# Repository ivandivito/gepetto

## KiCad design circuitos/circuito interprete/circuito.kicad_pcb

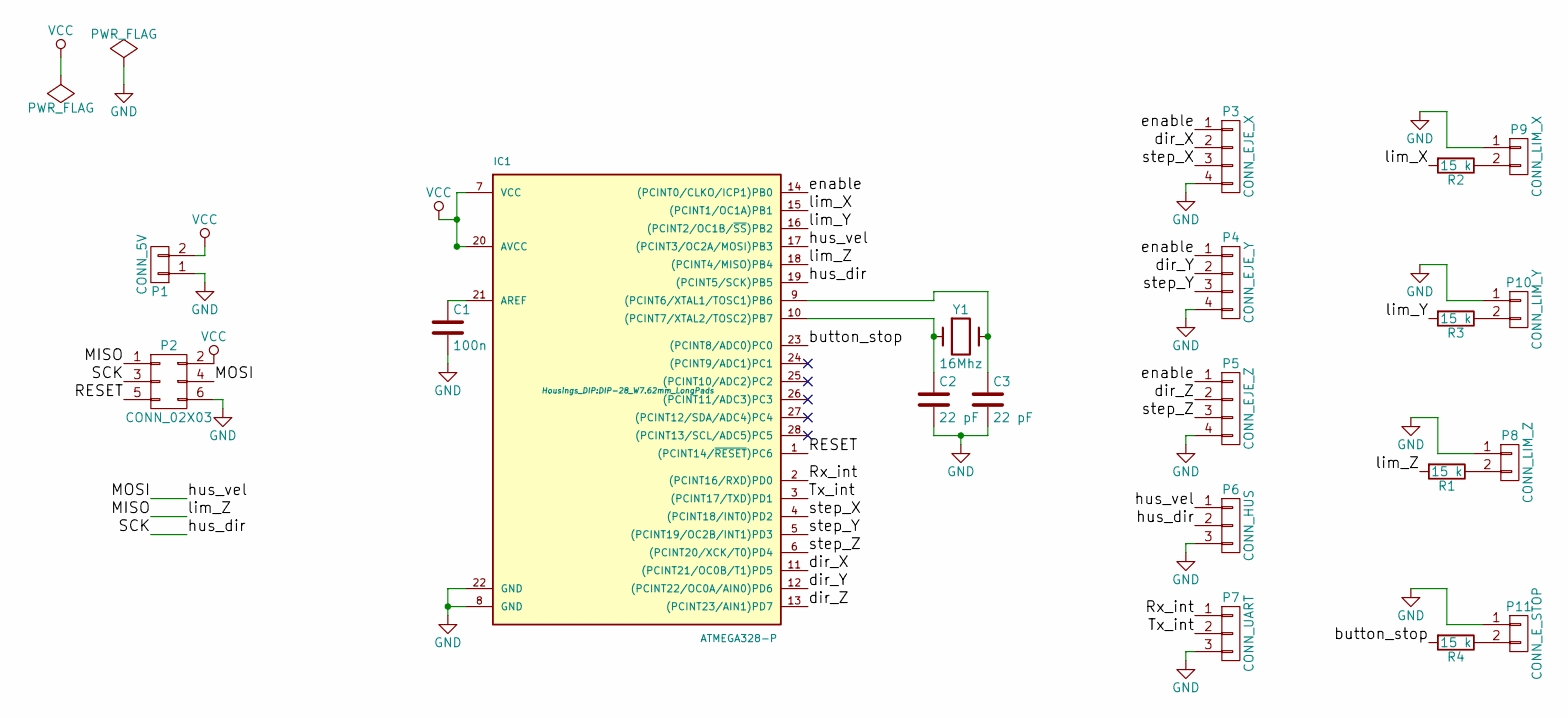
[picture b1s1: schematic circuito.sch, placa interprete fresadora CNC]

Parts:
C1: 100n; C_Disc_D3_P2.5
C2, C3: 22 pF; C_Disc_D3_P2.5
IC1: ATMEGA328-P; DIP-28_W7.62mm_LongPads
P1: CONN_5V; Pin_Header_Straight_1x02
P2: CONN_02X03; Pin_Header_Straight_2x03
P3: CONN_EJE_X; Pin_Header_Straight_1x04
P4: CONN_EJE_Y; Pin_Header_Straight_1x04
P5: CONN_EJE_Z; Pin_Header_Straight_1x04
P6: CONN_HUS; Pin_Header_Straight_1x03
P7: CONN_UART; Pin_Header_Straight_1x03
P8: CONN_LIM_Z; Pin_Header_Straight_1x02
P9: CONN_LIM_X; Pin_Header_Straight_1x02
P10: CONN_LIM_Y; Pin_Header_Straight_1x02
P11: CONN_E_STOP; Pin_Header_Straight_1x02
R1, R2, R3, R4: 15 k; Resistor_Horizontal_RM10mm
Y1: 16Mhz; Crystal_HC48-U_Vertical

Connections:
/MISO: IC1.18 ((PCINT4/MISO)PB4), P2.1, R1.2
/MOSI: IC1.17 ((PCINT3/OC2A/MOSI)PB3), P2.4, P6.1
/RESET: IC1.1 ((PCINT14/~RESET~)PC6), P2.5
/Rx_int: IC1.2 ((PCINT16/RXD)PD0), P7.1
/SCK: IC1.19 ((PCINT5/SCK)PB5), P2.3, P6.2
/Tx_int: IC1.3 ((PCINT17/TXD)PD1), P7.2
/button_stop: IC1.23 ((PCINT8/ADC0)PC0), R4.2
/dir_X: IC1.11 ((PCINT21/OC0B/T1)PD5), P3.2
/dir_Y: IC1.12 ((PCINT22/OC0A/AIN0)PD6), P4.2
/dir_Z: IC1.13 ((PCINT23/AIN1)PD7), P5.2
/enable: IC1.14 ((PCINT0/CLKO/ICP1)PB0), P3.1, P4.1, P5.1
/lim_X: IC1.15 ((PCINT1/OC1A)PB1), R2.2
/lim_Y: IC1.16 ((PCINT2/OC1B/~SS~)PB2), R3.2
/step_X: IC1.4 ((PCINT18/INT0)PD2), P3.3
/step_Y: IC1.5 ((PCINT19/OC2B/INT1)PD3), P4.3
/step_Z: IC1.6 ((PCINT20/XCK/T0)PD4), P5.3
GND: C1.2, C2.2, C3.2, IC1.8 (GND), IC1.22 (GND), P1.1, P2.6, P3.4, P4.4, P5.4, P6.3, P7.3, P8.1, P9.1, P10.1, P11.1
unnamed: C1.1, IC1.21 (AREF)
unnamed: C2.1, IC1.10 ((PCINT7/XTAL2/TOSC2)PB7), Y1.1
unnamed: C3.1, IC1.9 ((PCINT6/XTAL1/TOSC1)PB6), Y1.2
unnamed: P8.2, R1.1
unnamed: P9.2, R2.1
unnamed: P10.2, R3.1
unnamed: P11.2, R4.1
VCC: IC1.7 (VCC), IC1.20 (AVCC), P1.2, P2.2

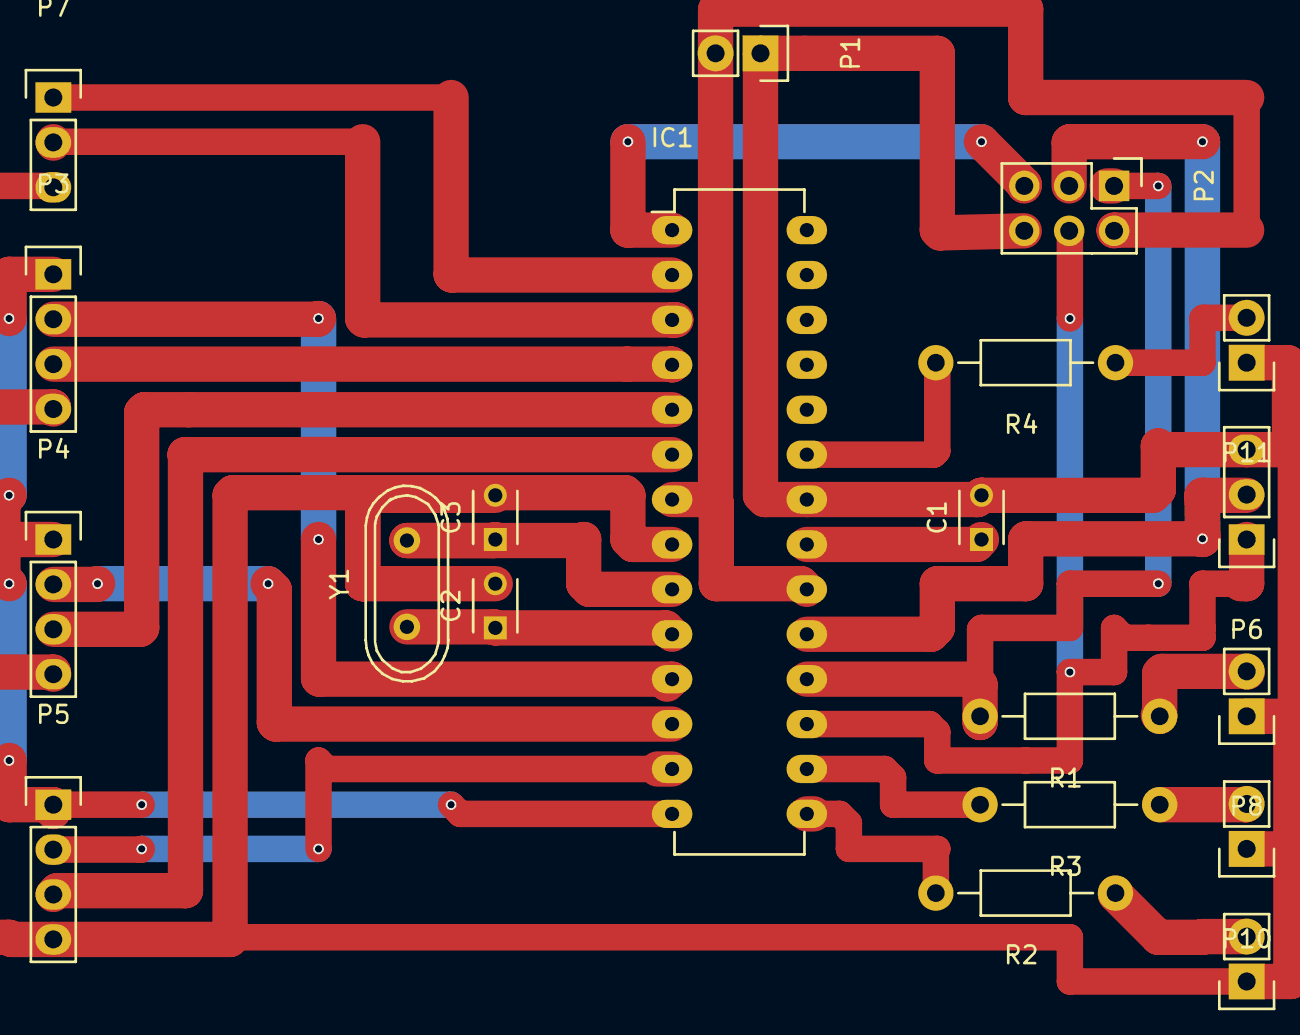
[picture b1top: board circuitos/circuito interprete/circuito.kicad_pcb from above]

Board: 2 copper layers, 20 parts (0 on the bottom side), 25 nets.

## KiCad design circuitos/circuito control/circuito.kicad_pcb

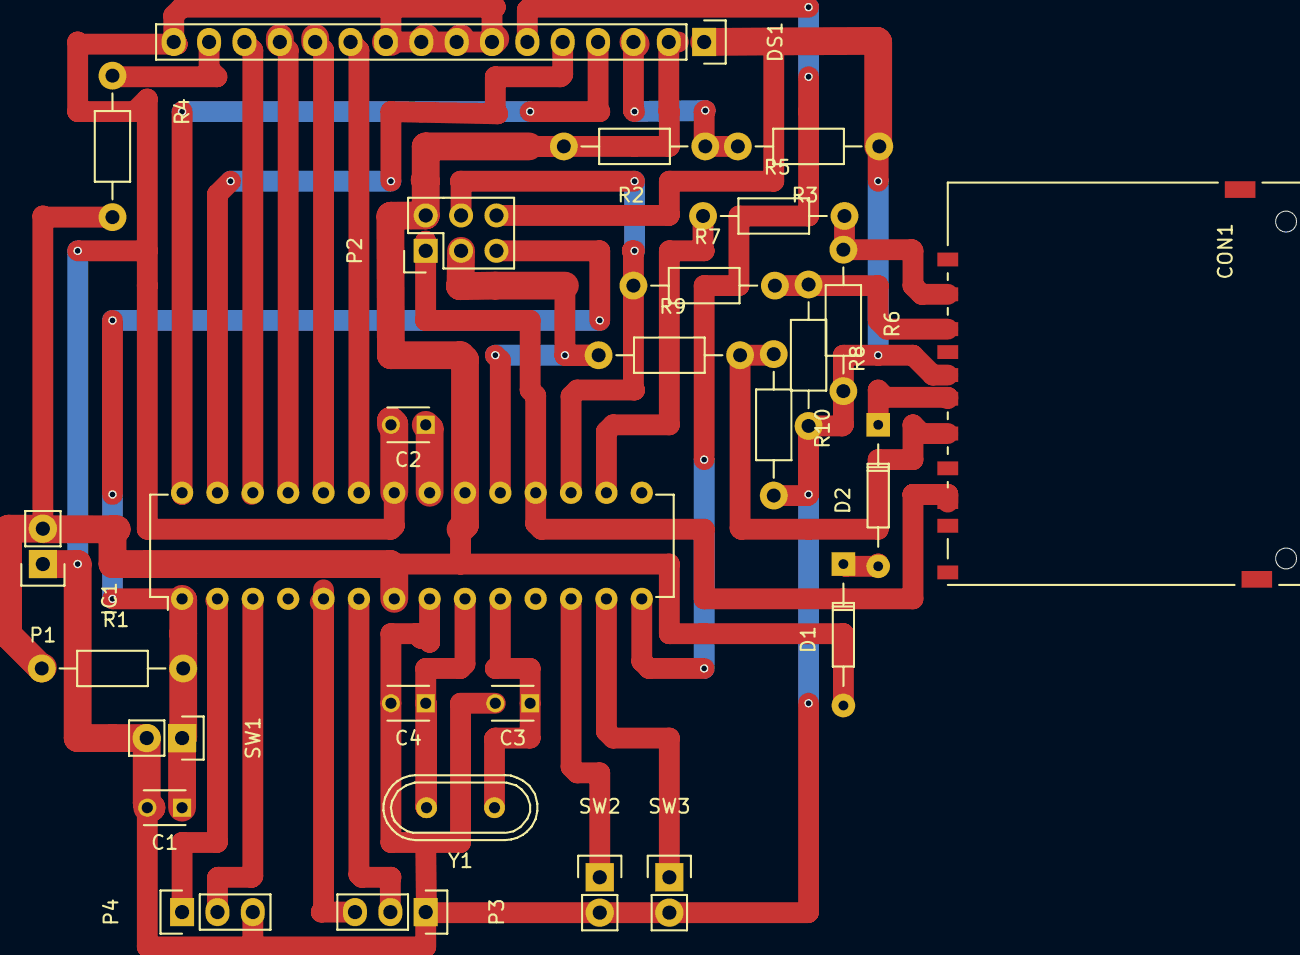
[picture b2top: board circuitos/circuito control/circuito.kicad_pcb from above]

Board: 2 copper layers, 27 parts (0 on the bottom side), 30 nets.

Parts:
C1: 100 n; C_Disc_D3_P2.5
C2: 100n; C_Disc_D3_P2.5
C3, C4: 22 pF; C_Disc_D3_P2.5
CON1: SD_Card; SD_Card_Receptacle
D1, D2: D; Diode_DO-35_SOD27_Horizontal_RM10
DS1: LCD16X2; Pin_Header_Straight_1x16
IC1: ATMEGA328-P; DIP-28_W7.62mm
P1: CONN_5V; Pin_Header_Straight_1x02
P2: CONN_02X03; Pin_Header_Straight_2x03
P3: CONN_UART_USB; Pin_Header_Straight_1x03
P4: CONN_UART; Pin_Header_Straight_1x03
R1: 15 K; Resistor_Horizontal_RM10mm
R2, R3: RVAR; Resistor_Horizontal_RM10mm
R4: 1 K; Resistor_Horizontal_RM10mm
R5, R7, R9: 4.7 K; Resistor_Horizontal_RM10mm
R6, R8, R10: 10 K; Resistor_Horizontal_RM10mm
SW1: B_RST_N_O; Pin_Header_Straight_1x02
SW2: B_SEL_N_O; Pin_Header_Straight_1x02
SW3: B_CHG_N_O; Pin_Header_Straight_1x02
Y1: 16Mhz; Crystal_HC49-U_Vertical

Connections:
/CLK_SD: CON1.5, R9.2, R10.1
/LCD_D_1: DS1.11, IC1.23
/LCD_D_2: DS1.12, IC1.24
/LCD_D_3: DS1.13, IC1.25
/LCD_D_4: DS1.14, IC1.26
/LCD_E: DS1.6, IC1.14
/LCD_R_S: DS1.4, IC1.28
/LCD_R_W: DS1.5, IC1.27
/MISO: CON1.7, IC1.18, P2.1
/MOSI: IC1.17, P2.4, R7.1
/MOSI_SD: CON1.2, R7.2, R8.1
/RESET: C1.1, IC1.1, P2.5, R1.2, SW1.1
/RX_USB: IC1.6, P3.2
/Rx_int: IC1.2, P4.1
/Rx_pc: IC1.5, P3.3
/SCK: IC1.19, P2.3, R9.1
/SS: IC1.16, R5.1
/SS_SD: CON1.1, R5.2, R6.1
/Tx_int: IC1.3, P4.2
/VDD: CON1.4, D2.1
/Vcc: D1.2, DS1.2, IC1.7, IC1.20, P1.2, P2.2, R1.1, R2.2, R4.2
/button_chg: IC1.13, SW3.1
/button_sel: IC1.12, SW2.1
GND: C1.2, C2.2, C3.2, C4.2, CON1.3, DS1.1, DS1.7, DS1.8, DS1.9, DS1.10, DS1.16, IC1.8, IC1.22, P1.1, P2.6, P3.1, P4.3, R3.1, R6.2, R8.2, R10.2, SW1.2, SW2.2, SW3.2
unnamed: C2.1, IC1.21
unnamed: C3.1, IC1.10, Y1.1
unnamed: C4.1, IC1.9, Y1.2
unnamed: D1.1, D2.2
unnamed: DS1.3, R2.1, R3.2
unnamed: DS1.15, R4.1

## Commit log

2015-10-23 agrego esquematicos circuitos
    agrego esquematicos de los circuitos interprete y controlador echos en
    kicad y exportados en PDF
2015-10-23 agrego anteproyecto
2015-10-29 agrego ruteo de placas
2015-10-30 Soft Uart
2015-10-31 cambios esquematicos varios
2015-10-31 Macros para buffers
2015-10-31 Adaptar Soft UART a atmega328p
2015-11-02 bug fixes
2015-11-02 Subrutinas para botones
2015-11-02 Bug fix
2015-11-04 cambios en el circuito de pull down.
2015-11-08 Separar subrutinas de estado
2015-11-08 Subrutinas de comunicacion USB y GRBL
2015-11-08 Bug fix, los botones ahora detectan flancos y no estado
2015-11-09 conexion spi y targeta SD
2015-11-10 Organizacion de archivos en includes
2015-11-13 Comparar strings en buffers
2015-11-13 Usb Timeout implemented
2015-11-13 Estado conectado reenvia datos
2015-11-13 Soft UART bug fixes
2015-11-14 Subi el datasheet del LCD
2015-11-14 ahi va el otro datasheet del LCD
2015-11-14 LCD y UI
2015-11-15 Tiempos de LCD optimizados
2015-11-15 Subrutinas para escribir en pantalla
2015-11-15 Escribir String en pantalla
2015-11-15 Interfaz basica en IDLE
2015-11-15 Saltos de estado por interfaz y bug fixing
2015-11-15 Timer de tiempo del sistema extendido
2015-11-18 sd comunication
2015-11-18 prueba UART
2015-11-18 documentacion de SD
2015-11-18 Ordenamiento UI
2015-11-20 Protocolo de transferencia de archivo implementado
2015-11-20 agrego estrctura del estado running
2015-11-20 agrego implementaciones de running
2015-11-20 Archivo transferido a la SD
2015-11-20 Fuentes programa PC
2015-11-20 agrego estado error
2015-11-20 la inicializacion de la SD ahora revisa si hay un programa en memoria
2015-11-21 fix bugs
2015-11-21 muchas cosas
2015-11-22 cambios de usb
2015-11-24 varios
2015-11-24 cambios soft uart
2015-11-24 adapto graficos para el informe
2015-11-28 cambio nombre estado
